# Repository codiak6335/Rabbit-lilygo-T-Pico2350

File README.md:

# Rabbit controller

The LilyGO T-Pico2350 is being replaced by two separate boards:

- Waveshare RP2350B Plus W, which will run the workout controller.
- Waveshare ESP32-C6-LCD-1.9, which will provide the display and network interface. The connected ESP identifies as an ESP32-C6FH8 with 8 MB flash. USB identifies the chip, but does not distinguish the LCD board variant.

## Inter-board UART wiring

The boards are already connected with three wires. Pin numbers in the left column are **physical header positions** on the RP2350 board, not GPIO numbers.

| RP2350B Plus W | Signal direction | ESP32-C6-LCD-1.9 |
| --- | --- | --- |
| Pin 1, GP0 / UART0 TX | RP2350 → ESP32-C6 | GPIO17 / UART RX |
| Pin 2, GP1 / UART0 RX | ESP32-C6 → RP2350 | GPIO16 / UART TX |
| Pin 3, GND | Common ground | GND |

The existing connection contains TX, RX, and ground; no RTS/CTS wires were specified. See the [Pico-compatible pinout](https://datasheets.raspberrypi.com/pico/Pico-2-Pinout.pdf) and [ESP32-C6-LCD-1.9 documentation](https://docs.waveshare.com/ESP32-C6-LCD-1.9).

## Printable enclosure

The [Rev D resin-window housing](mechanical/resin_housing/README.md) includes PETG body,
lid frame, window retainer and integral PCB standoffs, plus closed and split-wrap TPU strain
relief STLs for 2.3, 3, 3.5 and 4 mm cable jackets. It uses a cast clear resin
window, a silicone cord lid seal and two oversized cable entries for adhesive
sealing. Editable dimensions, print-fit coupons and assembly instructions are
included. The 82 × 128 × 33.1 mm prototype matches the `rev_d_case` 60 × 100 mm
PCB and its offset mounting hole, with the display centered, LED cable entry at
the top and power cable entry at the bottom. The captured KiCad reference is
checked during regeneration. Physical fit and splash/submersion qualification
remain to be performed.

## Current firmware status

The checked-in C++ firmware now targets this three-wire link. The RP2350 uses UART0 on GP0/GP1 without the LilyGO I²C expander startup; the ESP32-C6 uses UART0 on GPIO16/GPIO17 and sends its console output through USB Serial/JTAG. The ESP currently joins the provisioned `beaver` network and keeps `Rabbit-Test-6905` available as a fallback AP. The LCD shows live workout status and the Beaver DHCP address. The checked-in Coach On Deck browser UI is served at `/`, with repeatable pace/sprint set commands and NVS-backed saved sets; `/test` retains the manual diagnostics page. DeckScript plan transfer and surge pacing are flashed and passed paired-device HTTP/UART smoke tests; full browser and pool-side acceptance, external LEDs/audio, protected configuration editing, and hardware qualification remain unfinished. See [firmware/README.md](firmware/README.md) for build and diagnostic commands.

On this development host, the RP2350 appears as `/dev/ttyACM0` and the ESP32-C6 as `/dev/ttyACM1`. With the C++ firmware flashed, their stable serial-device names are:

```text
/dev/serial/by-id/usb-Raspberry_Pi_Pico_509E0DF26DCF56B6-if00
/dev/serial/by-id/usb-Espressif_USB_JTAG_serial_debug_unit_CC:BA:97:F2:69:04-if00
```

The 2026-09-25 paired-device smoke test passed: the ESP32-C6 USB console
reported `Rabbit RP2350 UART link: ready`, and the RP2350 USB `status` command
reported decoded UART requests and responses. The latest station/AP test joined
`beaver` at `192.168.0.178` and returned HTTP 200 for `/`, the browser assets,
pool and saved-set data, and `/api/set-status`. That DHCP address may change;
use the address displayed on the LCD. The fallback AP remains at
`http://192.168.4.1/` after joining `Rabbit-Test-6905`.

## Bluetooth speaker audio

Open **Deck tools → Audio output** in the ESP32 web interface. Audio uses the
same menu-row and Back-button navigation as the other settings.
Choose **Bluetooth speaker** to replace the buzzer or **Buzzer + speaker** for
both outputs. Output selection applies immediately. The volume slider applies
changes automatically as you move it; there is no Save button. Volume is 0–100
and saved volume is preserved. A GPIO active buzzer has a fixed level and is muted
at 0%.

The screen uses a familiar Bluetooth device picker: **My devices** keeps up to eight saved
speakers, including ones that are off or disconnected. Tap a saved device to reconnect
without scanning. Selecting another speaker, closing the page, or restarting either
board keeps all saved devices and their sound confirmations. **Forget** removes only
the device beside that control; forgetting an inactive device keeps the active speaker connected. To add a speaker:

1. Tap **Add speaker** to show **Nearby devices** and pairing instructions.
2. Power on the speaker and hold its Bluetooth button until the pairing indicator
   flashes. Disconnect it from your phone if needed. Tap **Scan** when ready.
   [MEGABOOM 3 pairing instructions](https://support.logi.com/hc/en-gb/articles/18601350410775-Getting-Started-MEGABOOM-3).
3. Tap the desired device in the list to connect directly. Bluetooth addresses
   distinguish devices with identical names; unnamed audio devices can also connect.
4. Once **Connected**, tap **Test 3 beeps**. Adjust volume and test again if needed.
5. Tap **I heard them** to record your sound confirmation. **I didn’t hear them**
   shows guidance to raise volume and repeat the test without confirming.

A scan searches Bluetooth Classic audio devices for about 20 seconds, then resolves
missing names, with a 45-second overall limit. It holds up to 16 devices. **Scan again**
starts fresh; **Stop scan** keeps the current results. Scanning keeps the existing
speaker association and output settings. A rejected Connect request changes neither
output nor volume. An unsuccessful or cancelled new connection retains the previous
saved speaker. **Close** or the screen's Back button stops discovery and cancels an unfinished
connection. Tap the saved speaker to reconnect. An unavailable saved speaker's
automatic reconnect does not block adding another device.
Setup/testing require an idle workout; discovery, connection, and active tests block
workout start. Errors remain visible until the next action.

Bluetooth Classic A2DP/SBC and AVRCP volume control run on the **RP2350B Plus W's CYW43439**.
The ESP32-C6 serves the UI and forwards commands over the existing UART link.
The workout's existing Audio choice gates the same beep signal for both outputs.
Bluetooth speaker buffering adds playback delay; pool-side timing still needs qualification.
While Bluetooth output is connected and unmuted, the RP2350 keeps A2DP streaming and
sends a quiet one-second 80 Hz maintenance pulse every 30 seconds, starting on connection.
The pulse is 1/128 of the workout tone's amplitude and fades in and out to avoid clicks.
It also runs between reps with five- or ten-minute gaps and while idle, to address
speakers that power down despite receiving silent packets. Workout/test beeps take
priority. Volume 0 mutes the pulse; Off, buzzer-only output, or Disconnect stops it.
The exact signal level needed to reset a speaker's inactivity timer is model-dependent;
the MEGABOOM's physical long-gap check remains to be verified. The keep-alive build
is flashed on the RP2350. Three native suites pass, including eleven-minute PCM
checks with five- and ten-minute rep gaps; a round trip through the actual Bluedroid
SBC encoder/decoder preserves the quiet pulse. Live UART/HTTP checks retained both
saved speakers and 49% volume, with the Samsung streaming and no fault recovery reported.
The buzzer remains available if a verified `RABBIT_AUDIO_PIN` is configured.
The development build has that pin disabled.

Output mode, volume, the selected speaker, the saved-device list, each device's sound
confirmation, and pairing keys persist on the RP2350. A full saved-device list does
not evict older speakers: forget one before adding another. Upgrading imports earlier
pairing keys, including devices replaced by the old single-speaker setting. Those keys
contain addresses only; names are recovered when the devices are reachable, and an
old confirmation overwritten by the previous firmware cannot be reconstructed. Settings saves wait until the workout is idle; the API reports pending
saves and the speaker's acknowledged volume. A saved speaker reconnects automatically
while idle when Bluetooth output is enabled. Disconnect suppresses reconnect until
requested again (or the controller restarts); Forget removes the association and its
link key. Confirmation requires a completed test on the currently streaming speaker;
a disconnected or interrupted test cannot be confirmed.

ESP32 HTTP API (commands return current audio status; Devices returns a discovery page):

| Method | Route | Body / query |
| --- | --- | --- |
| GET | `/api/audio/status` | none |
| GET | `/api/audio/saved?offset=0` | saved devices, offset 0–8; up to four results per page |
| POST | `/api/audio/config` | `{"mode":"bluetooth","volume":50}`; modes `off`, `buzzer`, `bluetooth`, `both` |
| POST | `/api/audio/scan` | empty |
| GET | `/api/audio/devices?offset=0` | offset 0–16; up to four results per page |
| POST | `/api/audio/scan-stop` | empty |
| POST | `/api/audio/connect` | `{"address":"C0:28:8D:DC:C9:3D","mode":"bluetooth","volume":49}`; scanned or saved address, mode `bluetooth` or `both` |
| POST | `/api/audio/test` | empty |
| POST | `/api/audio/confirm` | empty; only after a completed speaker test |
| POST | `/api/audio/disconnect` | empty |
| POST | `/api/audio/forget` | `{"address":"C0:28:8D:DC:C9:3D"}` removes that saved speaker; empty body removes the selected speaker |
| POST | `/api/audio/pair` | Legacy exact-name pairing; `{"name":"MEGABOOM 3"}`, empty body uses that name |

Status includes `mode`, `volume`, `connection`, `name`, `address`, `supported`,
`buzzerAvailable`, `paired`, `volumeConfirmed`, `actualVolume`, `testActive`,
`settingsPending`, `soundConfirmed`, `workoutRunning`, and `lastError`.
`actualVolume` is null until acknowledged. Device pages include `scanning`, `full`,
`total`, `devices` (name/address/rssi), and `next` (next offset or null). Saved pages
include `total`, `full`, `devices` (name/address/soundConfirmed), and `next`.
Invalid payloads return 400, unavailable/busy commands 409, unavailable Bluetooth 501,
and a failed UART exchange 503. Scan and Connect are asynchronous; poll Devices and
Status respectively. UI requests have an eight-second response timeout. Slider changes are debounced
200 ms and sent in order; the final slider value is applied even if it changes
while an earlier request is in flight. Output selections apply immediately.

The RP2350 UART API uses the existing version-1 CRC/COBS frames and Hello session.
Message IDs 12–17 remain AudioStatus, AudioConfigure, AudioPair, AudioDisconnect,
AudioTest, and AudioForget. IDs 18–22 add AudioScan, AudioDevices, AudioConnect,
AudioConfirm, and AudioScanStop. IDs 23–24 add AudioSaved and AudioForgetDevice.
Saved takes a one-byte offset; ForgetDevice takes a six-byte address. Configure carries mode/volume bytes; legacy Pair
carries 1–48 name bytes without NUL/control characters. Devices takes a one-byte
offset; Connect takes `[address[6], mode=2|3, volume=0..100]`. Other commands have
empty payloads. Success returns AudioStatus except Devices, which returns AudioDevices.
Request/session IDs are preserved; failures use the existing Reject format.
The status payload remains `[version=1, mode, volume, connection, flags, actualVolume,
lastError, nameLength, address[6], name[nameLength]]`. Connection values 0–6 are
disabled, idle, scanning, connecting, connected, streaming, error. Flag bits 0–7
are supported, buzzer available, paired, volume confirmed, test active, save pending,
sound confirmed, workout running. Unknown actual volume is 255.
Devices payload is `[version=1, scanning, full, total, offset, count, records...]`;
Saved uses the same page header with scanning=0 and replaces RSSI with a 0/1 sound-confirmed byte.
Discovery records are `[nameLength, address[6], signedRssi, name[nameLength]]` (RSSI 0 means
unknown). Four maximum-length records fit in 230 bytes. UART retries reuse IDs and
cannot restart scans, connections, tests, or confirmations. Version-2 audio settings
retain compatibility with previously saved version-1 settings and Bluetooth keys.

Radio GPIOs are GP36 (enable), GP37 (data/host wake), GP38 (CS), and GP39 (clock),
verified against the [Waveshare schematic](https://files.waveshare.com/wiki/RP2350B-Plus-W/RP2350B-Plus-W.pdf).
The LED output uses PIO1 to keep its low GPIO range separate from the radio's high GPIOs.
Large LED/UART buffers reside in static RAM; the foreground stack reserves 4 KiB.
The radio uses foreground CYW43 polling so Bluetooth callbacks and UART commands share
one execution context. Both AVRCP roles are initialized to handle the speaker's control
messages. A four-second watchdog recovers a stalled controller; USB `status` reports
the last recovery stage and captured fault location.
Pairing/settings use the SDK's two flash TLV banks near the end of the 16 MiB flash;
avoid erasing that storage when preserving saved audio settings.

The 2026-10-04 saved-device build is installed on both boards. Native protocol/workout
checks pass (2/2), including saved-list storage validation, pagination, retaining
multiple speakers, and forgetting one device without removing another. Mobile browser
checks cover retained device lists, reconnecting without a scan, per-device Forget,
automatic volume/output changes, connection errors, sound confirmation, workout gating,
scan cancellation, and Back navigation. The installed ESP32 UI displays both the
Samsung Soundbar MS650 and the recovered MEGABOOM pairing, with separate Connect/Forget
controls; the disconnected MEGABOOM remains listed after a page reload. A further
RP2350 reboot retained both records, the Samsung sound confirmation, selected speaker,
and 49% volume; the soundbar resumed streaming. The MEGABOOM's old link key contains
its address but not the name or confirmation overwritten by the old single-device
setting. Earlier live checks verified automatic MEGABOOM volume changes and real
discovery/cancellation. Pool-side latency remains to be qualified. The ESP32 address
for these checks was `http://192.168.0.166/`; use the current LCD address if DHCP changes it.

## Wi-Fi Defaults

The default Wi-Fi password is `1234567890`.

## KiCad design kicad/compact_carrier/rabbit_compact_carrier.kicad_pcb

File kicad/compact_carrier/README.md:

# Compact two-board carrier — placement study

Open [`rabbit_compact_carrier.kicad_pro`](rabbit_compact_carrier.kicad_pro) in KiCad. This is a new project in the Rabbit repository; [`../proto`](../proto) remains untouched as a visual/mechanical reference. `proto` has two Pico 2 W footprints and cannot be used as the electrical design for the RP2350B-Plus-W and ESP32-C6-LCD-1.9 pair.

The first candidate outline is **88 × 58 mm**, compared with about 89.2 × 57 mm for `proto` and 115 × 92 mm for the earlier powered-carrier draft. The two existing modules and all future components are intended to mount on the **front/top face**. This does not mean single-layer copper: the file starts as a two-layer PCB. Both module USB-C sockets face the left board edge. The right-hand rectangles reserve space for the DROK, 12 V input, and LED/buzzer connection, but are **drawings, not populated footprints**.

J1/J2 represent the ESP's two 1×20 socket rows; J3/J4 represent the RP board's rows. The three verified UART/GND nets are assigned to the first three pads of J1/J3 but **are not routed**. All other pads are intentionally unconnected. The local `Rabbit_Carrier.pretty` footprint library is included so the project is self-contained. Its row pitch and pad size come from the prior carrier draft; the actual two boards, socket height, pin orientation, body envelopes, LCD overhang, antenna clearance, and USB cable clearance still need a full-size print/physical fit check.

**PLACEMENT ONLY — DO NOT FABRICATE OR POWER.** There is no KiCad schematic, safe power/USB coexistence circuit, protection circuitry, connector footprints, mounting-hole solution, DRC sign-off, or fabrication output. The compact right-hand reserve may need to grow when those parts are selected. In particular, do not connect DROK 5 V to either module while a PC USB cable is attached until the power-isolation design has been captured and verified.

Next design gate: confirm whether both module USB connections must remain connected to computers while the 12 V/DROK supply powers both boards. That choice determines the power/USB architecture and whether this outline can be retained.

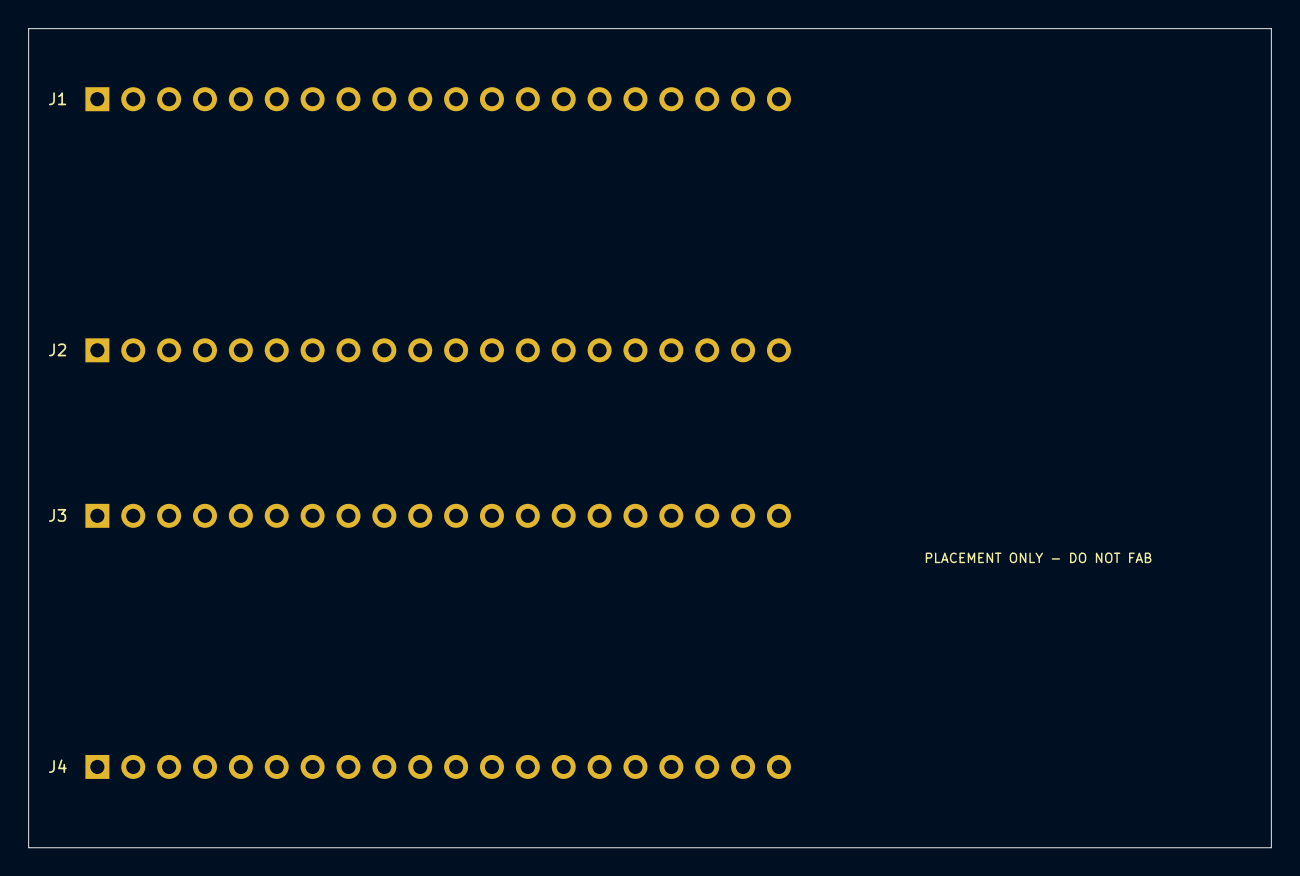
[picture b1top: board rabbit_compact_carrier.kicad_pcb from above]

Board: 2 copper layers, 88.0 x 58.0 mm, 4 parts (0 on the bottom side), 3 nets, no tracks yet.

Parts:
J1: ESP_IO16_IO17_ROW; Socket_1x20_Horizontal
J2: ESP_OPPOSITE_ROW; Socket_1x20_Horizontal
J3: RP_GP0_GP1_ROW; Socket_1x20_Horizontal
J4: RP_OPPOSITE_ROW; Socket_1x20_Horizontal

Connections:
ESP_IO16_TO_RP_GP1: J1.1, J3.2
GND: J1.3, J3.3
RP_GP0_TO_ESP_IO17: J1.2, J3.1

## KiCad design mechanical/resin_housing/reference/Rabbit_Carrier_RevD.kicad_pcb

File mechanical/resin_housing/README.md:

# Rev D housing with cast-resin viewing lid

Printable housing for the **`rev_d_case` 60 × 100 mm carrier PCB**, with a clear resin window centered over the ESP32 display. The assembled shell is **82 × 128 × 33.1 mm**, excluding the cable boots. Viewed with the screen facing you, the **LED cable exits the top end** and **power enters the bottom end**. Both glands share the case and display centreline at **X = 30 mm**, with internal leads running to J6 and J5. Both entries accept the same relief neck; choose reliefs for **2.3, 3.0, 3.5 or 4.0 mm complete cable jacket diameters**.

This replaces the earlier 88 × 58 mm compact-carrier housing. PCB outline, mounting holes and socket positions are checked against the captured [Rev D KiCad board](reference/Rabbit_Carrier_RevD.kicad_pcb). Module heights, actual LCD datum and sealing still require first-article checks. **Physical fit and leak testing have not been performed; it has no verified waterproof/IP rating.** Print the coupons first, then qualify frequent splashes and brief submersion up to 3 ft.

## Files and print quantities

All STL dimensions are millimetres. Each STL is already placed on the print bed in its intended orientation. Import at 100% scale.

| Part | Quantity | Material / purpose |
| --- | ---: | --- |
| [Body](stl/body_petg.stl) | 1 | PETG; open side up; blind insert pockets, cord groove and four integral Rev D standoffs |
| [Lid frame](stl/lid_frame_petg.stl) | 1 | PETG; outside face down; doubles as the resin casting frame |
| [Window retainer](stl/window_retainer_petg.stl) | 1 | PETG; sealant groove faces up in the slicer, toward the lid in assembly |
| [Cable entry coupon](stl/cable_entry_fit_coupon_petg.stl) | 1 optional | PETG; reproduces the horizontal bore and 8 mm wall thickness |
| [Resin casting coupon](stl/resin_cast_fit_coupon_petg.stl) | 1 optional | PETG; small version of the cast window flange |
| [Coupon retainer](stl/resin_coupon_retainer_petg.stl) | 1 optional | PETG; tests mechanical retention and the resin/PETG seal |
| [Unused entry plug](stl/unused_entry_plug_tpu.stl) | As needed | TPU; seal into any unused entry |
| Cable reliefs below | 1 per cable | TPU; inside flange on the bed, cable bore vertical |

| Cable jacket outside diameter | Closed relief | Split wrap relief | Nominal bore |
| --- | --- | --- | ---: |
| 2.3 mm | [STL](stl/strain_relief_2_3mm_closed_tpu.stl) | [STL](stl/strain_relief_2_3mm_split_wrap_tpu.stl) | 2.5 mm |
| 3.0 mm | [STL](stl/strain_relief_3_0mm_closed_tpu.stl) | [STL](stl/strain_relief_3_0mm_split_wrap_tpu.stl) | 3.2 mm |
| 3.5 mm | [STL](stl/strain_relief_3_5mm_closed_tpu.stl) | [STL](stl/strain_relief_3_5mm_split_wrap_tpu.stl) | 3.7 mm |
| 4.0 mm | [STL](stl/strain_relief_4_0mm_closed_tpu.stl) | [STL](stl/strain_relief_4_0mm_split_wrap_tpu.stl) | 4.2 mm |

Closed reliefs can be fitted before feeding the cable through. Split wraps open along a 0.4 mm radial seam for already terminated cables; that seam must be filled and sealed. The specified wire sizes refer to the **complete insulated jacket**, not the conductor diameter. A common jacket around multiple conductors needs its own measured relief bore.

## Dimensions and hardware assumptions

See [dimensions.svg](dimensions.svg) for the plan. Coordinates below follow the carrier drawing: X right, Y down; Z up from the outside bottom of the enclosure.

| Feature | Nominal dimension |
| --- | --- |
| Carrier PCB | Rev D, 60 × 100 × 1.6 mm |
| PCB mounting holes | Ø2.7 mm at (4,4), (56,4), (4,96), **(45,96)** |
| Integral standoffs | Ø6 mm, 2.5 mm above the floor; Ø2.0 mm blind pilots for M2.5 plastic-tapping screws |
| PCB underside | Z = 5.5 mm; 2.5 mm clearance over the 3 mm floor |
| Space above PCB | 22 mm to lid; 20 mm under the window retainer |
| Estimated LCD front plane | 18.35 mm above PCB top; 1.65 mm below the retainer, 3.65 mm below the resin |
| Viewing opening | Rev D provisional aperture, 43.5 × 23.5 mm, corner radius 1 mm |
| Viewing opening centre | Carrier X = 30, Y = 50 mm |
| Cast resin | 4 mm thick at the viewing opening; 55.5 × 35.5 × 2.4 mm rear flange, corner radius 3 mm |
| Resin amount | About 6.3 mL net; allow for mixing/cup losses |
| Window retainer | 63.5 × 43.5 × 2 mm; continuous 1.2 mm wide × 0.6 mm deep sealant groove |
| Retainer screw centres | (11,30.25), (49,30.25), (11,69.75), (49,69.75); clear of RF exclusions |
| Cable holes | Ø8.6 mm through the 8 mm top and bottom end walls |
| LED entry | Top end (−Y), centered at X = 30; wall spans Y = −14 to −6; cable axis Z = 15 |
| Power entry | Bottom end (+Y), centered at X = 30; wall spans Y = 106 to 114; cable axis Z = 15 |
| Relief neck / collar | Ø7.4 mm neck, 8.3 mm between collar faces; Ø12 mm collars |
| Glue clearance | 0.6 mm radial gap around relief neck; 0.1 mm nominal radial gap around cable |
| Relief length | 33.8 mm total; approximately 24 mm projects outside the case |
| Main gasket | 2 mm silicone cord in a 2.8 × 1.5 mm groove; nominal 25% squeeze at the flat rim stop |
| Gasket centreline length | About 367 mm; cut/join to the actual printed groove |

The ESP board envelope is 51 × 26 mm at carrier X=1.86, Y=37; the RP2350 is 51 × 21 mm at X=1.86, Y=69.5, with a 4.92 mm radio extension to the right. The visible display centre is (30,50), while the ESP PCB centre is (27.36,50). The 2.64 mm offset comes from the Rev D case datum: J3 pad 1 + (26.77,8.89). The active display is 42.72 × 22.70 mm and clears the modeled opening. Confirm the first article against [Waveshare dimensions](https://docs.waveshare.com/ESP32-C6-LCD-1.9); the Rev D documentation flags the manufacturer archive's S3-named mechanical model as provisional for the C6 board.

The four standoffs match the carrier's real mounting holes, including the deliberately offset lower-right hole. USB connectors remain enclosed; for USB service, remove the lid and lift the controller from its sockets to give the plug room. Both end-wall glands are centered at X=30; route their internal leads to J6 at the top and J5 at the bottom. The lid and base remain intact. Verify actual cable jacket diameters, collar installation, wiring bends, socket engagement and assembled module height before printing the full body. The LCD face height is the Rev D estimate; RP and DROK heights are conservative illustrative reservations, not measured assemblies.

Both ends have 6 mm clearance for the inner cable collars and wiring. Side clearance accommodates the resin flange/retainer; the 8 mm rim provides room for the cord seal and lid screws outside it. The shell adds about 24 mm of external boot projection at each end.

The RP RF exclusion is (52.78,62.25)–(71.28,97.75); the ESP exclusion is (47,43)–(60,57). Case fasteners are checked against both regions, and the lower retainer screws are moved inward accordingly. The RP exclusion extends 11.28 mm past the PCB edge: the plastic wall may occupy this area, but keep wires, added electronics, metal mounting hardware and conductive coatings clear.

## Materials and fasteners

- PETG for body, lid and retainer; this version is sized for PETG printing. A change to PP requires new fit and adhesive trials.
- TPU, starting with 95A, for reliefs and unused-port plugs. Softer TPU may ease installation, but fit must be checked on the coupon.
- Optically clear two-part casting epoxy suitable for a **4 mm section**, with the manufacturer's mixing ratio and full cure time. For example, read the [clear casting epoxy technical sheet](https://www.smooth-on.com/tb/files/EPOXACAST_690_692_TB.pdf) when choosing resin; optical clarity, sunlight exposure and adhesion need your own coupon trial.
- Flexible neutral-cure sealant compatible with the specific cured resin, PETG, TPU and cable jacket. Confirm adhesion and immersion suitability on the coupons.
- Approximately 380 mm of 2 mm silicone cord, with a sealed end joint, or a custom continuous silicone gasket matching the groove.
- Four M3 heat-set inserts, nominal 4.6 mm outer diameter × 4 mm long; the body pilot pockets are Ø4.4 × 4.2 mm. Match the actual insert supplier's hole recommendation before printing.
- Four M3 × 8 mm button-head machine screws. The lid has Ø6.4 × 1.8 mm head recesses; use heads that fit them.
- Four M2 × 5 mm plastic-tapping screws for the window retainer, using Ø1.7 mm blind pilots. The casting coupon uses four more M2 × 5 screws temporarily.
- Four M2.5 × 6 mm plastic-tapping screws for the PCB, using its existing Ø2.7 mm clearance holes and the standoffs' Ø2.0 mm blind pilots. Their nominal engagement is 4.4 mm, leaving about 1.1 mm of solid base underneath. Qualify thread grip before installing the board.

## Printing

Start with a 0.4 mm nozzle, 0.2 mm layers, six PETG perimeters and solid floor/lid layers. Use at least 15 bottom layers for the 3 mm floor, and 100% infill for the frame and retainer. Use four TPU perimeters and 100% infill; print the reliefs upright as supplied. These are starting settings, not a waterproof process specification.

The body and cable coupon have horizontal circular bores. Inspect sagging and clean the bore gently; qualify relief fit using the coupon printed with the same profile. The other parts have no enclosed support cavities. Keep supports out of the cord groove, casting pocket and cable bore. A small brim can help the upright coupon and TPU parts.

Inspect printed seams and layer bonding. Seal any porosity with a compatible thin coating and keep gasket lands flat and clean. FDM watertightness depends on the print process; see [Prusa's watertight-print experiments](https://blog.prusa3d.com/watertight-3d-printing-pt1-vases-cups-and-other-open-models_48949/). Do not treat a watertight STL mesh as evidence of a watertight print.

## Casting and assembly

1. Print the cable and resin coupons and the required relief diameter. Check the fit on the actual cable, collar insertion, glue filling, resin cure and sealant adhesion. The coupon has a 20 × 14 mm viewing opening with the same 4 mm optical thickness and 2.4 mm rear flange construction.
2. Print the full lid. Its outside face is the flat face that was on the print bed; its inside face contains the larger stepped casting pocket. Clean the pocket and prepare the PETG bond surfaces as required by the resin/sealant supplier.
3. Place the outside face **down on flat, release-treated glass**, leaving the stepped inside pocket facing up. Hold the frame flat and seal the temporary mould contact so resin cannot escape under it. Keep mould release off the permanent bond surfaces. Pour through the central opening and fill the larger rear pocket flush with the inside face. The glass forms the smooth optical face; the wider pocket forms the retaining flange. Cast with the electronics removed and allow full cure.
4. Clean flash from the window and inspect it. Fill the retainer's continuous groove with compatible sealant. The groove straddles the resin/PETG seam when the ring is installed. Put the ring against the inside lid, **groove toward the lid**, and use the four M2 × 5 screws. Tighten gently and cure the sealant. The rear ring supports inward water pressure on the resin flange; the outer PETG ledge prevents outward movement. The sealant closes the seam.
5. Install the four M3 inserts flush with the body rim. Avoid disturbing the adjacent cord groove. Fit the silicone cord, sealing its joined ends; its compression is set by the lid touching the flat rim.
6. Fit each TPU relief with the smaller flat flange inside and the tapered boot outside. Try folding the inner TPU collar through the coupon before committing to the case. Closed reliefs are installed before feeding the cable; split wraps can be opened around it. Seal the entire neck-to-wall annulus, cable-to-bore gap, and split seam over the collar/neck region. Use continuous intact cable jacket at the seal. Cure fully. Seal a TPU plug into an unused entry.
7. Leak-test the empty enclosure with dry paper inside: frequent splashes, then brief submersion progressing to the intended maximum of 3 ft. Gently move the cables during testing and inspect the window seam, cable entries, cord joint and printed walls. Fix and retest any ingress before installing electronics.
8. Place the Rev D carrier on the four standoffs with J6 at the LED end and J5 at the power end. The lower-right hole is at X=45, not X=56. Use four M2.5 × 6 screws through the PCB holes. Keep cable routing away from the antenna zones. Check real display height/alignment, cable bends and clearance under the retainer. Close using the four M3 lid screws evenly until the rim meets; avoid crushing the PETG or over-tightening plastic-tapping screws.

## Editing and regenerating

The editable design is [parameters.json](parameters.json) plus [generate_resin_housing.py](generate_resin_housing.py). Change assembled clearance, resin window dimensions or cable positions there. PCB datums are tied to the captured [Rev D board](reference/Rabbit_Carrier_RevD.kicad_pcb), copied from `/home/codiak/hgfs/vmshared/Rabbit_Carrier/rev_d_case/`. The [original case plan](reference/RevD_Case_Plan.svg) and [display alignment](reference/RevD_Horizontal_Alignment.svg) record the mechanical datum assumptions. The original plan's wiring arrows mark PCB connection positions; this housing uses centered glands as specified in `parameters.json`. The SHA-256 identifies the exact PCB input. A different board revision requires a new source reference and reviewed mounting/module datums.

The generator checks source checksum, PCB outline/thickness, all four mount holes/drills, socket rows, DROK origin, module placement and LCD centre against the KiCad file. It exports 15 STLs, the dimension drawing, previews and [validation.json](validation.json), checking connected watertight meshes, winding, exported STL reloads, assembly collisions, print-bed placement, LCD visibility, correct top LED/bottom power assignment and case-metal clearance from both RF exclusions. Both window and carrier screw holes are blind; only the two sealed cable holes open through the shell.

```sh
python3 -m venv /tmp/rabbit-housing-venv
/tmp/rabbit-housing-venv/bin/pip install -r mechanical/resin_housing/requirements.txt
/tmp/rabbit-housing-venv/bin/python mechanical/resin_housing/generate_resin_housing.py
```

To generate a variant without overwriting these files:

```sh
/tmp/rabbit-housing-venv/bin/python mechanical/resin_housing/generate_resin_housing.py \
  --parameters /path/to/variant.json --output /tmp/rabbit-housing-variant
```

The obsolete corner-clip STL from the compact-carrier design has been removed. Use this release's complete body/lid/retainer set together. A fit-check failure is a reason to inspect the changed geometry. The released files passed all geometric checks with the supplied parameters. Sealing, screw grip, resin adhesion and print tolerances still require the physical trials described above.

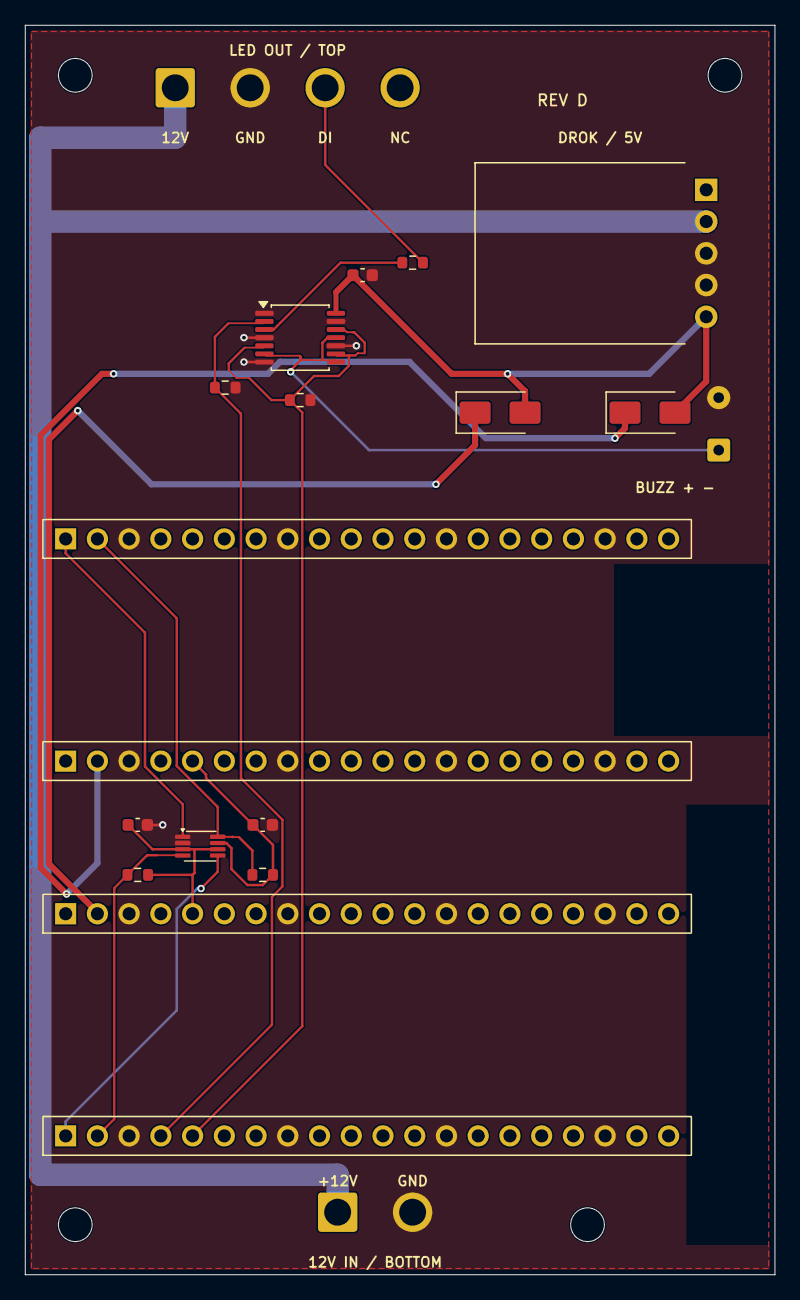
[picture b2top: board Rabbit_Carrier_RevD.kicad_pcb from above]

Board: 2 copper layers, 60.0 x 100.0 mm, 24 parts (0 on the bottom side), 16 nets.

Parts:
C4, C5, C8: 100n_25V_X7R; C_0603_1608Metric
D2: SS24_RP_VSYS; D_SMA
D3: SS24_ESP_VSYS; D_SMA
H1, H2, H3, H4: M2.5_NPTH; MountingHole_2.7mm_M2.5
J1: RP_L_20P; Bossie_BX-PM2.54-1-20PY
J2: RP_R_20P; Bossie_BX-PM2.54-1-20PY
J3: ESP_L_20P; Bossie_BX-PM2.54-1-20PY
J4: ESP_R_20P; Bossie_BX-PM2.54-1-20PY
J5: 12V_INPUT_HARDWIRE; SolderWire-1.5sqmm_1x02_P6mm_D1.7mm_OD3mm
J6: LED_STRIP_HARDWIRE; SolderWire-1.5sqmm_1x04_P6mm_D1.7mm_OD3mm
J9: BUZZER_DIRECT_AHCT; SolderWire-0.25sqmm_1x02_P4.2mm_D0.65mm_OD1.7mm
MOD1: DROK_12V_TO_5V_PROVISIONAL; DROK_200548_5pad_PROVISIONAL
R3, R4, R5, R10: 10k; R_0603_1608Metric
R6: 330; R_0603_1608Metric
U2: TXU0202_UART_ISOLATOR; TXU0202_DCU_RowMask
U4: SN74AHCT125PW; TSSOP-14_4.4x5mm_P0.65mm

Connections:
12V_IN: J5.1, J6.1, MOD1.2
BUZZ_BUF: J9.1, U4.6, U4.8, U4.11
DROK_5V: C8.1, D2.2, D3.2, MOD1.5, U4.14
ESP_3V3: C5.1, J4.5, R4.2, U2.7
ESP_RX: J3.2, R4.1, U2.8
ESP_TX: J3.1, U2.1
ESP_VSYS: D3.1, J4.2
GND: C4.2, C5.2, C8.2, J1.3, J1.8, J1.13, J1.18, J2.3, J2.8, J2.13, J2.18, J3.3, J3.8, J3.13, J3.18, J4.3, J4.8, J4.13, J4.18, J5.2, J6.2, J9.2, MOD1.3, MOD1.4, R5.2, R10.2, U2.2, U4.1, U4.4, U4.7, U4.10, U4.13
LED_BUF: R6.1, U4.3
LED_DI: J6.3, R6.2
RP_3V3: C4.1, J2.5, R3.2, U2.3, U2.6
RP_BUZZ: J1.5, R10.1, U4.5, U4.9, U4.12
RP_LED: J1.4, R5.1, U4.2
RP_RX: J1.2, R3.1, U2.4
RP_TX: J1.1, U2.5
RP_VSYS: D2.1, J2.2
